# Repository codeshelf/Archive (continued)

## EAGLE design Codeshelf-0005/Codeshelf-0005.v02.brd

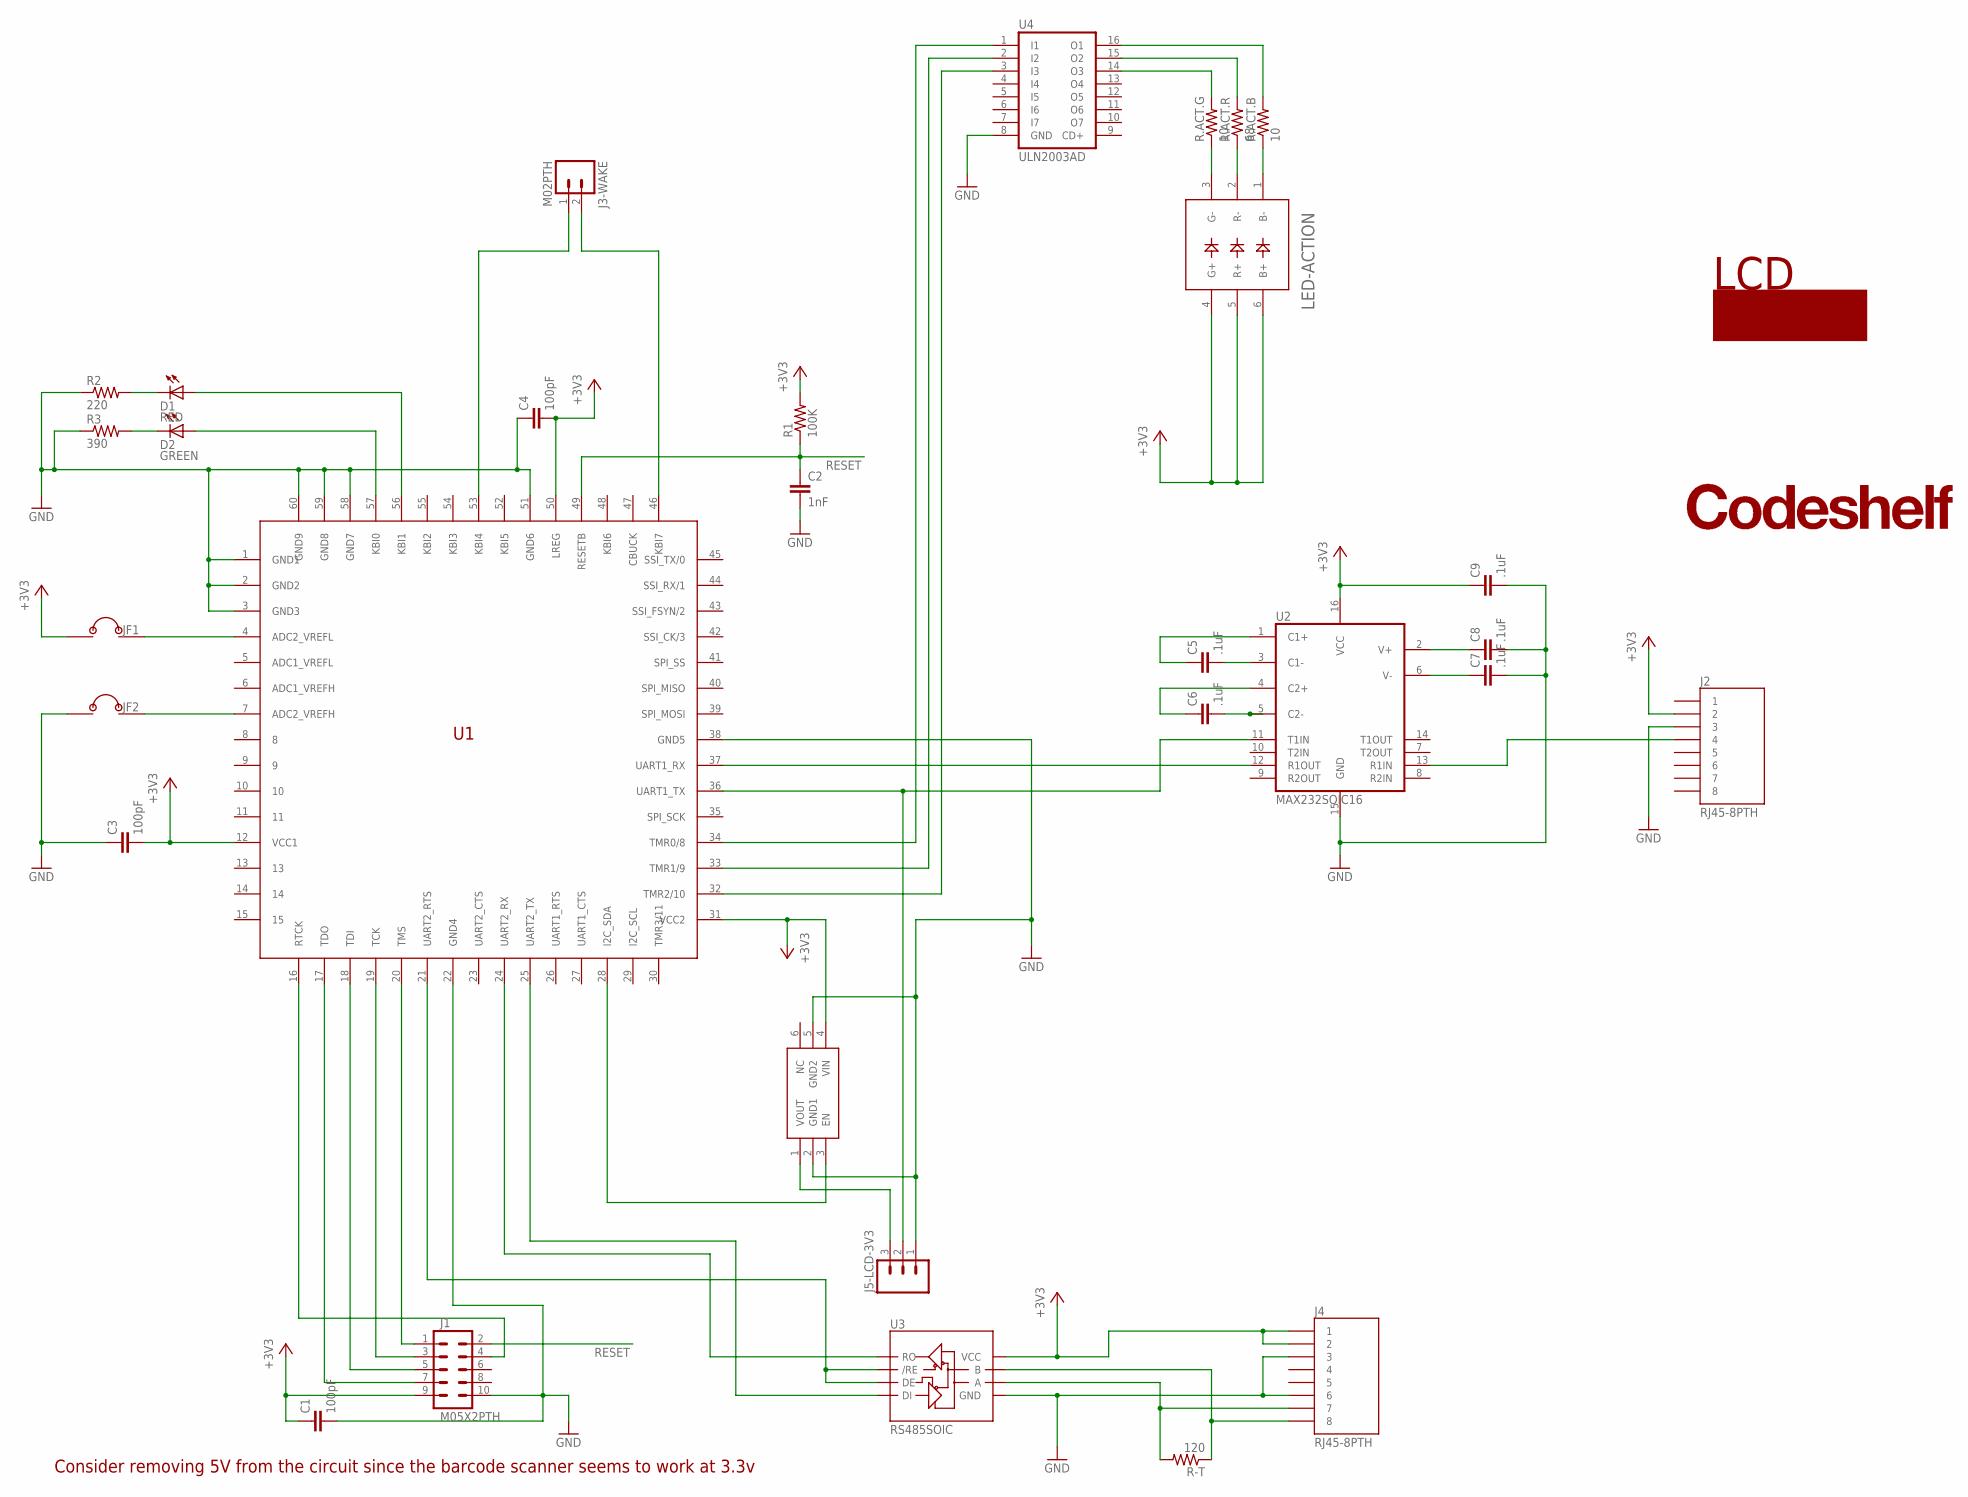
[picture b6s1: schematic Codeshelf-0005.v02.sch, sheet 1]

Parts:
C1, C3, C4: 100pF; C0603
C2: 1nF; C0603
C5, C6, C7, C8, C9: .1uF; C0402
D1: RED; CHIP-LED0805
D2: GREEN; CHIP-LED0805
J1: M05X2PTH; AVR_ICSP
J2, J4: RJ45-8PTH; RJ45-8
J3-WAKE: M02PTH; 1X02
J5-LCD-3V3: M03PTH; 1X03
JF1, JF2: JUMPER-2X-SMT-VIA; JUMPER-VIA-2X
LCD: LCD-SPARKFUN; LCD-20X4-SPARKFUN
LED-ACTION: LED5060A; PLCC-6
LOGO: CODESHELF-LOGO
R1: 100K; RF-R0402
R2: 220; RF-R0402
R3: 390; RF-R0402
R-T: 120; RF-R0402
R.ACT.B, R.ACT.G: 10; RF-R0402
R.ACT.R: 68; RF-R0402
U1: ZSFM201-1A; ZSFM201-1
U2: MAX232SOIC16; SO016
U3: RS485SOIC; SO08
U4: ULN2003AD; SO16
U6: MIC94061C6; SC70-6L

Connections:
+3V3: C1.1, C3.2, C4.2, C9.1, J1.9, J2.2, J4.1, J4.2, JF1.1, LED-ACTION.4 (G+), LED-ACTION.5 (R+), LED-ACTION.6 (B+), R1.2, U1.12 (VCC1), U1.31 (VCC2), U1.50 (LREG), U2.16 (VCC), U3.8 (VCC), U6.4 (VIN); also elsewhere on the board
C1: C5.1, U2.1 (C1+)
C2: C6.1, U2.4 (C2+)
GND: C1.2, C2.2, C3.1, C4.1, C7.2, C8.2, C9.2, J1.10, J2.3, J4.3, J4.6, J5-LCD-3V3.1, JF2.1, R2.1, R3.1, U1.1 (GND1), U1.2 (GND2), U1.3 (GND3), U1.22 (GND4), U1.38 (GND5), U1.51 (GND6), U1.58 (GND7), U1.59 (GND8), U1.60 (GND9), U2.15 (GND), U3.5 (GND), U4.8 (GND), U6.2 (GND1), U6.5 (GND2); also elsewhere on the board
unnamed: D2.A, U1.57 (KBI0)
unnamed: D1.A, U1.56 (KBI1)
unnamed: D2.C, R3.2
unnamed: D1.C, R2.2
unnamed: JF2.2, U1.7 (ADC2_VREFH)
unnamed: JF1.2, U1.4 (ADC2_VREFL)
unnamed: C5.2, U2.3 (C1-)
unnamed: U1.28 (I2C_SDA), U6.3 (EN)
unnamed: J5-LCD-3V3.3, U6.1 (VOUT)
unnamed: C6.2, U2.5 (C2-)
unnamed: C7.1, U2.6 (V-)
unnamed: J3-WAKE.2, U1.46 (KBI7)
unnamed: C8.1, U2.2 (V+)
unnamed: J3-WAKE.1, U1.53 (KBI4)
unnamed: U1.25 (UART2_TX), U3.4 (DI)
unnamed: U1.24 (UART2_RX), U3.1 (RO)
unnamed: U1.21 (UART2_RTS), U3.2 (/RE), U3.3 (DE)
unnamed: J4.8, R-T.1, U3.7 (B)
unnamed: J4.7, R-T.2, U3.6 (A)
unnamed: R.ACT.R.2, U4.15 (O2)
unnamed: R.ACT.G.2, U4.14 (O3)
unnamed: LED-ACTION.1 (B-), R.ACT.B.1
unnamed: LED-ACTION.2 (R-), R.ACT.R.1
unnamed: LED-ACTION.3 (G-), R.ACT.G.1
unnamed: U1.34 (TMR0/8), U4.1 (I1)
unnamed: U1.33 (TMR1/9), U4.2 (I2)
unnamed: R.ACT.B.2, U4.16 (O1)
unnamed: U1.32 (TMR2/10), U4.3 (I3)
R1IN: J2.4, U2.13 (R1IN)
R1OUT: U1.37 (UART1_RX), U2.12 (R1OUT)
RESET: C2.1, J1.2, R1.1, U1.49 (RESETB)
RTCK: J1.4, U1.16 (RTCK)
T1IN: J5-LCD-3V3.2, U1.36 (UART1_TX), U2.11 (T1IN)
TCK: J1.3, U1.19 (TCK)
TDI: J1.5, U1.18 (TDI)
TDO: J1.7, U1.17 (TDO)
TMS: J1.1, U1.20 (TMS)

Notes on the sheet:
Consider removing 5V from the circuit since the barcode scanner seems to work at 3.3v

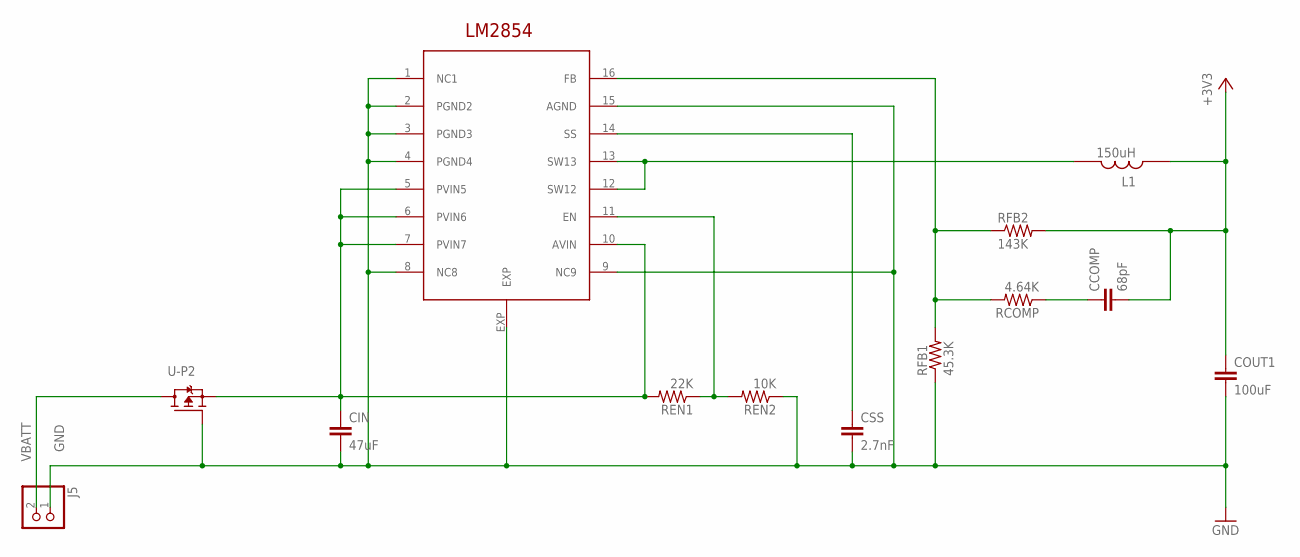
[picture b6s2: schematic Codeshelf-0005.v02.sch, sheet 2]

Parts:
CCOMP: 68pF; C0805
CIN: 47uF; C1210K
COUT1: 100uF; C1210K
CSS: 2.7nF; C0805
J5: PINHD-1X2/90; 1X02/90
L1: 150uH; SLF10165
RCOMP: 4.64K; RF-R0402
REN1: 22K; RF-R0402
REN2: 10K; RF-R0402
RFB1: 45.3K; RF-R0402
RFB2: 143K; RF-R0402
U-P1: LM2854MH; HTSSOP16PWP
U-P2: PCHANNEL-MOSFET-DPAK; DPAK

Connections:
+3V3: CCOMP.2, COUT1.1, L1.2, RFB2.2; also elsewhere on the board
GND: CIN.2, COUT1.2, CSS.2, J5.1, REN2.1, RFB1.1, U-P1.1 (NC1), U-P1.2 (PGND2), U-P1.3 (PGND3), U-P1.4 (PGND4), U-P1.8 (NC8), U-P1.9 (NC9), U-P1.15 (AGND), U-P1.EXP, U-P2.1 (G); also elsewhere on the board
unnamed: CSS.1, U-P1.14 (SS)
unnamed: L1.1, U-P1.12 (SW12), U-P1.13 (SW13)
unnamed: RCOMP.2, RFB1.2, RFB2.1, U-P1.16 (FB)
unnamed: CCOMP.1, RCOMP.1
unnamed: REN1.1, REN2.2, U-P1.11 (EN)
V-PROT: CIN.1, REN1.2, U-P1.5 (PVIN5), U-P1.6 (PVIN6), U-P1.7 (PVIN7), U-P1.10 (AVIN), U-P2.3 (S)
VBATT: J5.2, U-P2.4 (D)

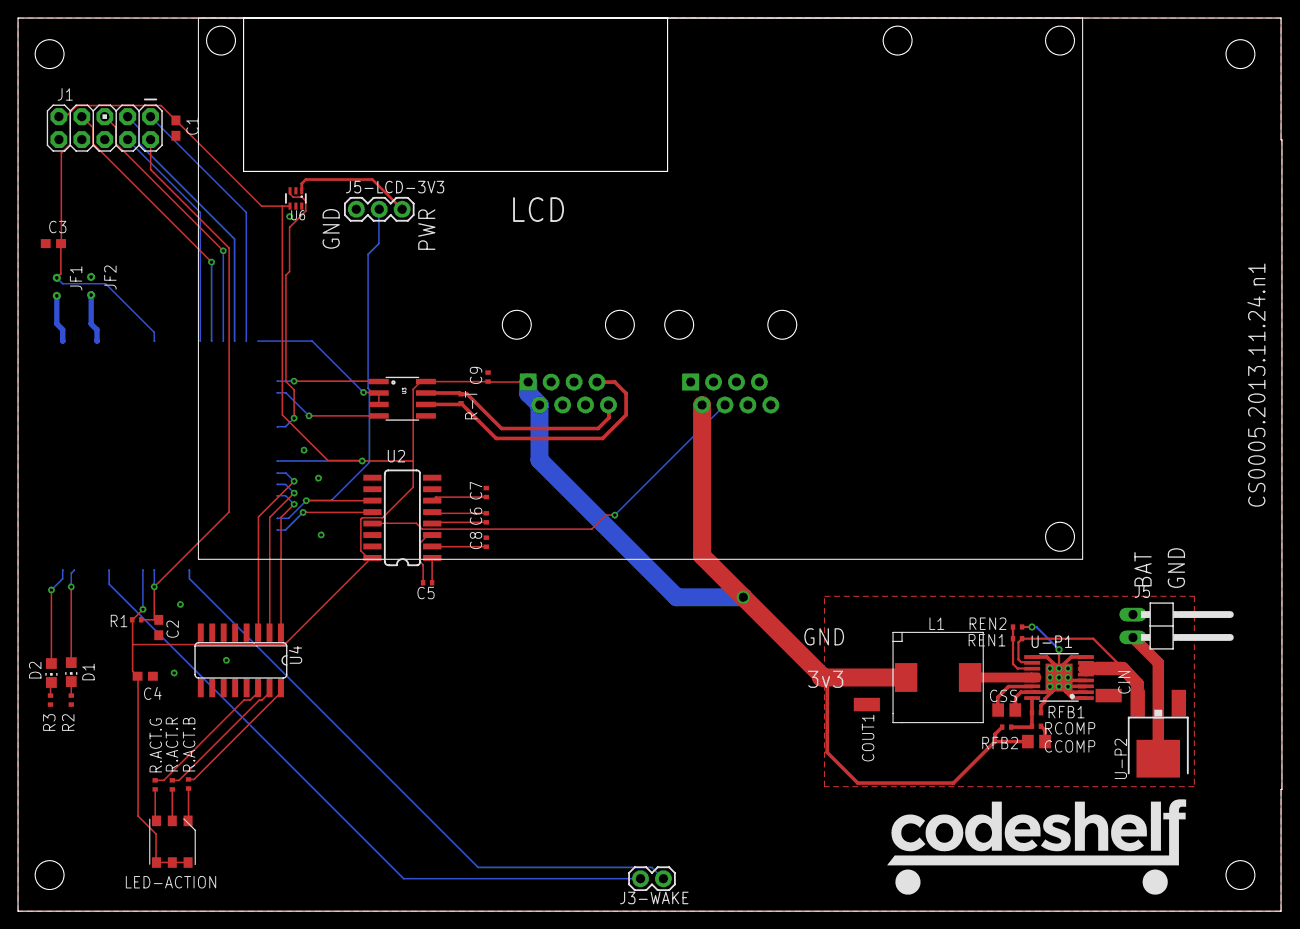
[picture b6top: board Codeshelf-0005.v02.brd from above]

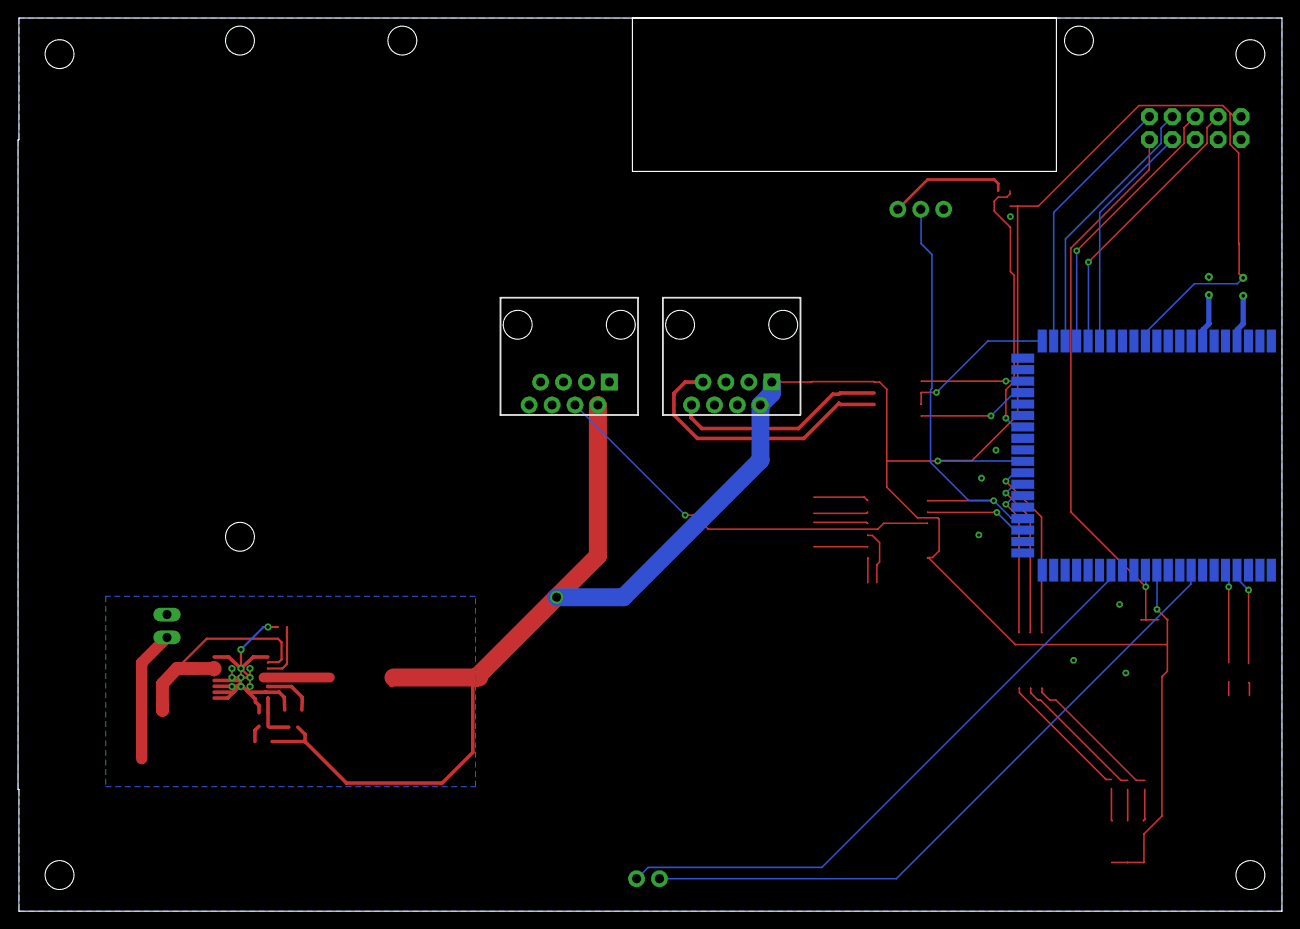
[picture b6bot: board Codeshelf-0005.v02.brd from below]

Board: 2 copper layers, 140.1 x 99.0 mm, 46 parts (3 on the bottom side), 48 nets.

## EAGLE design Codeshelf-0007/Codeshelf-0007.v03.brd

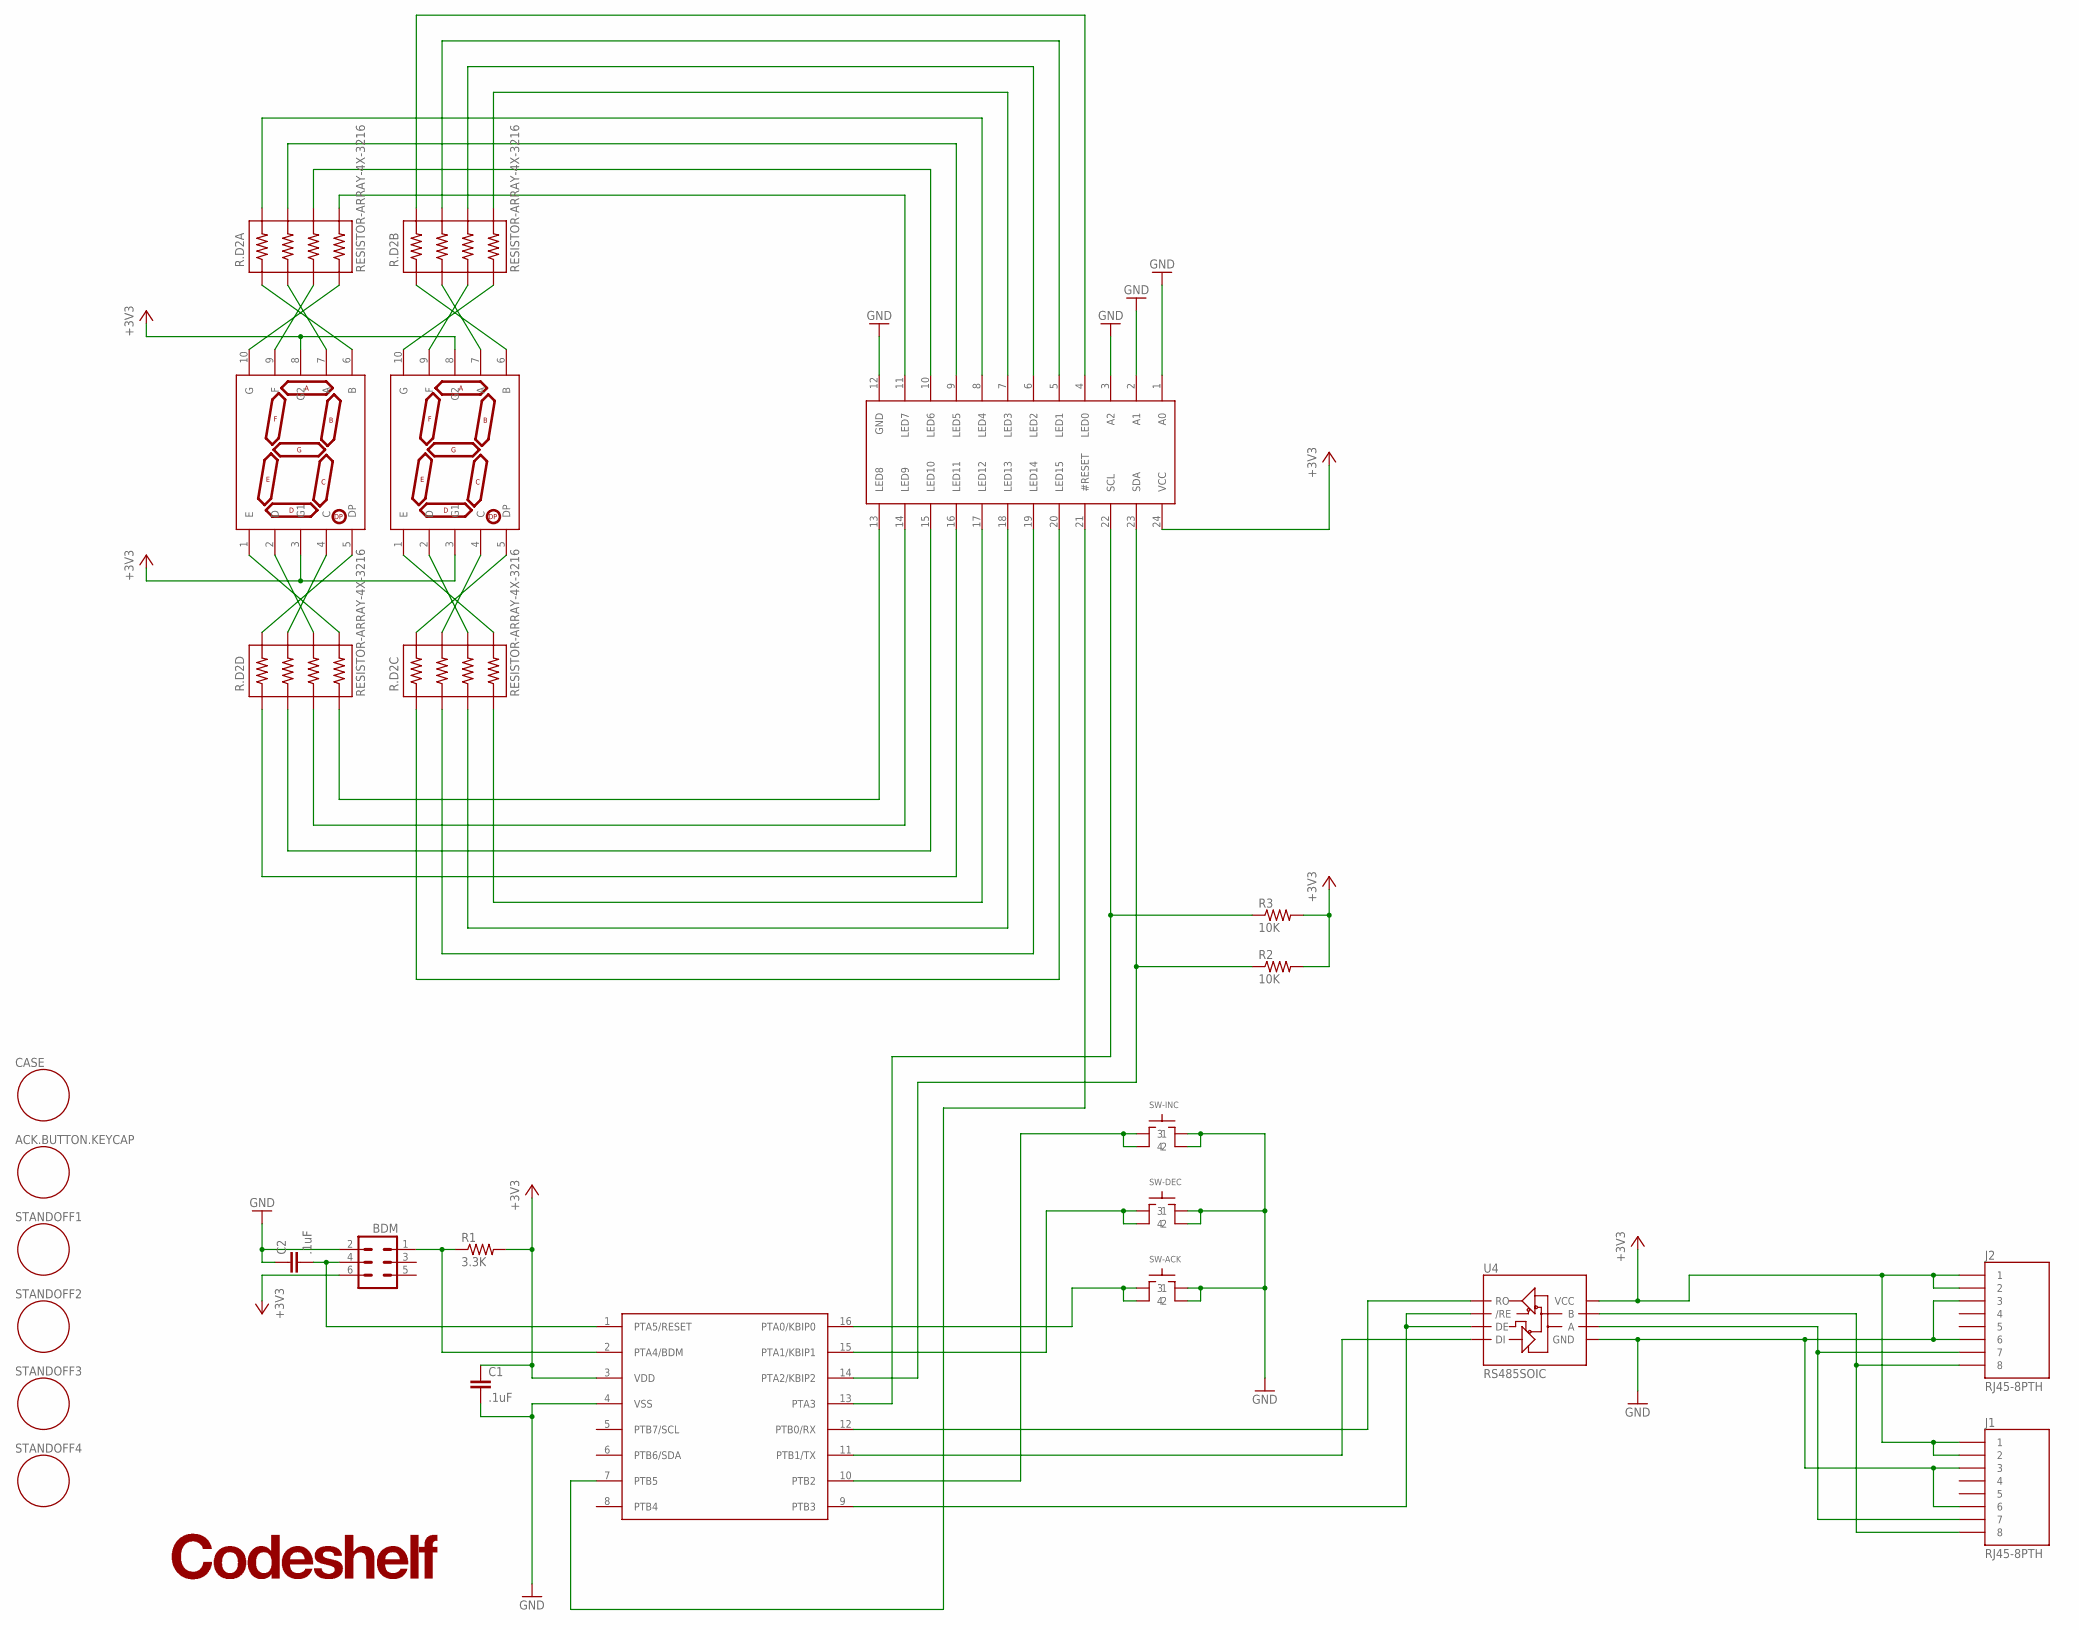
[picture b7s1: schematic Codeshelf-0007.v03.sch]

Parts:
ACK.BUTTON.KEYCAP: EXTERNAL-COMPONENT
BDM: HEADER-3X2
C1, C2: .1uF; C0402
CASE: EXTERNAL-COMPONENT; MFGP PN-1321-C
J1, J2: RJ45-8PTH; RJ45-8
LED1, LED2: 7SEGMENT-1DIGITSMD; 7SEGMENT-1DIG-.40-SMD
LOGO: CODESHELF-LOGO
R1: 3.3K; RF-R0402
R2, R3: 10K; RF-R0402
R.D2A, R.D2B, R.D2C, R.D2D: RESISTOR-ARRAY-4X-3216; 3216-4X
STANDOFF1, STANDOFF2, STANDOFF3, STANDOFF4: EXTERNAL-COMPONENT
SW-ACK: SWITCH-TACTILE-320.03E11
SW-DEC: SWITCH-TACTILE-FSM
SW-INC: SWITCH-TACTILE-FSM
U2: MC9S08QG-DT; TSSOP16
U3: CAT9552; TSSOP24
U4: RS485SOIC; SO08

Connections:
+3V3: BDM.6, C1.1, J1.1, J1.2, J2.1, J2.2, LED1.3 (G1), LED1.8 (G2), LED2.3 (G1), LED2.8 (G2), R1.2, R2.2, R3.2, U2.3 (VDD), U3.24 (VCC), U4.8 (VCC)
GND: BDM.2, C1.2, C2.1, J1.3, J1.6, J2.3, J2.6, SW-ACK.P$3 (3), SW-ACK.P$4 (4), SW-DEC.P$3 (3), SW-DEC.P$4 (4), SW-INC.P$3 (3), SW-INC.P$4 (4), U2.4 (VSS), U3.1 (A0), U3.2 (A1), U3.3 (A2), U3.12 (GND), U4.5 (GND)
unnamed: R.D2A.5 (4B), U3.11 (LED7)
unnamed: R.D2A.6 (3B), U3.10 (LED6)
unnamed: R.D2A.7 (2B), U3.9 (LED5)
unnamed: R.D2A.8 (1B), U3.8 (LED4)
unnamed: R.D2B.5 (4B), U3.7 (LED3)
unnamed: SW-ACK.P$1 (1), SW-ACK.P$2 (2), U2.16 (PTA0/KBIP0)
unnamed: SW-DEC.P$1 (1), SW-DEC.P$2 (2), U2.15 (PTA1/KBIP1)
unnamed: SW-INC.P$1 (1), SW-INC.P$2 (2), U2.10 (PTB2)
unnamed: BDM.1, R1.1, U2.2 (PTA4/BDM)
unnamed: R.D2B.6 (3B), U3.6 (LED2)
unnamed: R.D2B.7 (2B), U3.5 (LED1)
unnamed: R.D2B.8 (1B), U3.4 (LED0)
unnamed: LED2.6 (B), R.D2A.1 (1A)
unnamed: LED2.7 (A), R.D2A.2 (2A)
unnamed: LED2.9 (F), R.D2A.3 (3A)
unnamed: LED2.10 (G), R.D2A.4 (4A)
unnamed: LED2.5 (DP), R.D2D.8 (1B)
unnamed: LED2.4 (C), R.D2D.7 (2B)
unnamed: U2.9 (PTB3), U4.2 (/RE), U4.3 (DE)
unnamed: LED2.2 (D), R.D2D.6 (3B)
unnamed: LED2.1 (E), R.D2D.5 (4B)
unnamed: LED1.6 (B), R.D2B.1 (1A)
unnamed: BDM.4, C2.2, U2.1 (PTA5/RESET)
unnamed: LED1.7 (A), R.D2B.2 (2A)
unnamed: LED1.9 (F), R.D2B.3 (3A)
unnamed: LED1.10 (G), R.D2B.4 (4A)
unnamed: LED1.5 (DP), R.D2C.8 (1B)
unnamed: LED1.4 (C), R.D2C.7 (2B)
unnamed: LED1.2 (D), R.D2C.6 (3B)
unnamed: LED1.1 (E), R.D2C.5 (4B)
unnamed: R.D2D.4 (4A), U3.13 (LED8)
unnamed: R.D2D.3 (3A), U3.14 (LED9)
unnamed: R.D2D.2 (2A), U3.15 (LED10)
unnamed: R.D2D.1 (1A), U3.16 (LED11)
unnamed: R.D2C.4 (4A), U3.17 (LED12)
unnamed: R.D2C.3 (3A), U3.18 (LED13)
unnamed: R.D2C.2 (2A), U3.19 (LED14)
unnamed: R.D2C.1 (1A), U3.20 (LED15)
RESET: U2.7 (PTB5), U3.21 (#RESET)
RS485_N: J1.8, J2.8, U4.7 (B)
RS485_P: J1.7, J2.7, U4.6 (A)
RX: U2.12 (PTB0/RX), U4.1 (RO)
SLA: R2.1, U2.14 (PTA2/KBIP2), U3.23 (SDA)
SLC: R3.1, U2.13 (PTA3), U3.22 (SCL)
TX: U2.11 (PTB1/TX), U4.4 (DI)

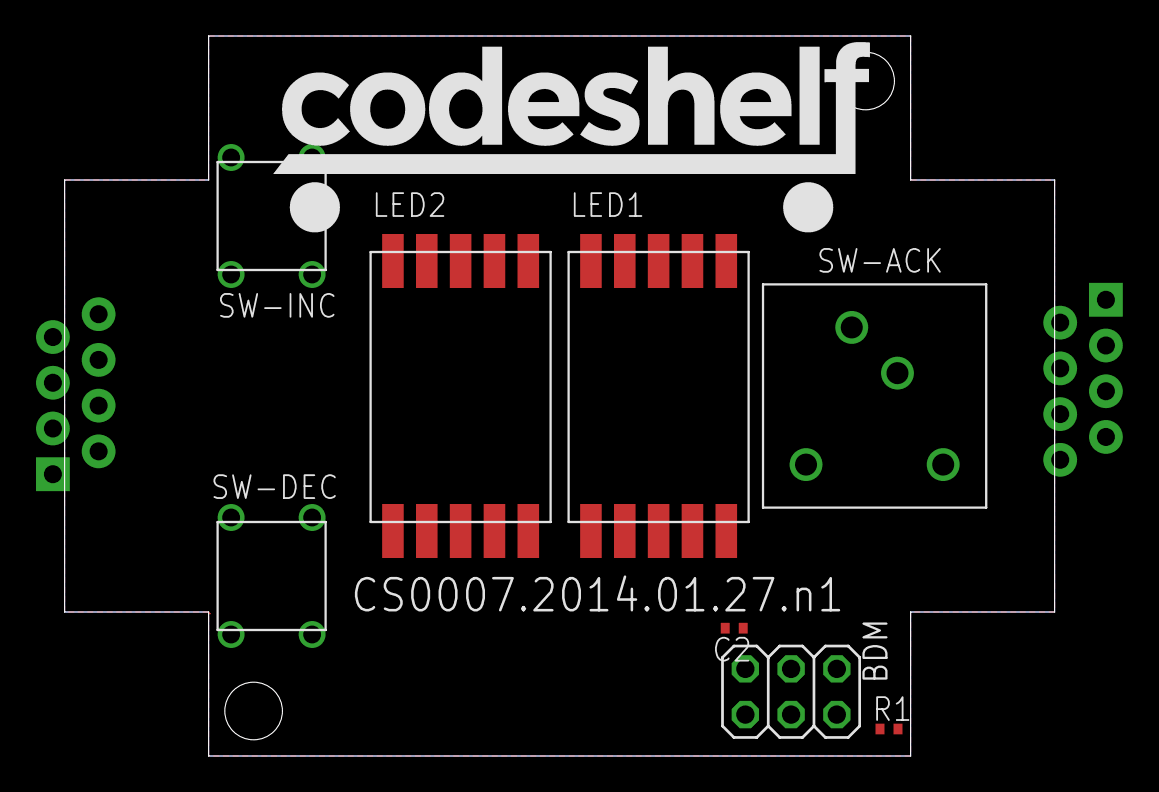
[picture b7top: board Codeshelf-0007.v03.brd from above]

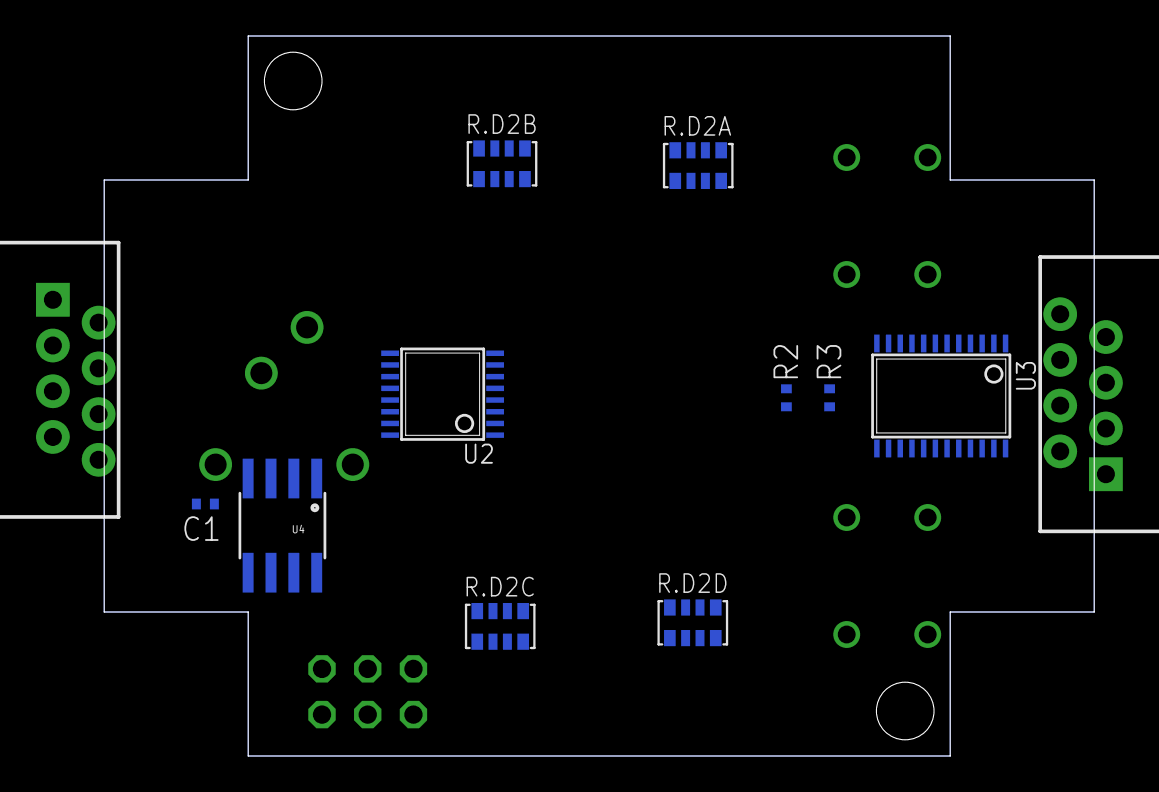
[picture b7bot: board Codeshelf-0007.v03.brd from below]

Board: 2 copper layers, 55.0 x 40.0 mm, 27 parts (12 on the bottom side), 47 nets.

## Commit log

2013-10-22 First commit
    Converted the CAD files to Eagle 6.5 XML project files and committed
    them to the repo.
2013-10-23 cleanup repo
    Cleaned up repo.
    Cleaned up GW-devices.lbr
    Add CS0012 - gateway dongle
    CS0011 board changed to match laser from Laser66.
2013-10-23 Flip the JTAG port
    flip the JTAG port.
    Change the LCD holes from pads to drills.
2013-11-05 Changes related to design review with Ravi and Charlie.
    Mainly we need a new way to connect all of the boards where the cables
    enter the back.
2013-11-23 CHE controller changes for Ravi & Charlie feedback
    RS485 3V/GND on two conductors
    Scanner pins separated from RS485 pins on EN patch cables.
    Sleep switch and power control of scanner the LCD display
2013-11-23 Position controller bus rewiring
    The position controller's RS495 bus rewired to support double 3.3V/GND
    and to be off of the same pins as the scanner. (Matches the change
    with the CHE controller.)
2013-11-24 Move the scanner and rs485 connectors to fit around either battery holder type
2013-11-25 Changes reviewed with Charlie
2013-11-27 BOM review before first articles of 0005, 0007, 0008, 0012
    Reviewed BOM with Charlie
2013-11-29 BOMs as Excel files
2013-11-30 ignore xlsx# files.
2013-11-30 gitignore fixup
2013-11-30 Parts changes for C1, C2 and C7
2014-03-31 New position controller design
2014-03-31 New KW2 Radio design
    First schematic and test layout
2014-04-11 Remove 5V SMPS
2014-04-15 Add CAM files
2014-05-23 SlotFlex Pos. Controller, SMPS
    Copied position controller elements to Slotflex schematic. Corrected
    inductor value typo in SMPS.
2014-05-27 Fixed FB resistor label
    Made FB1/FB2 resistor label consistent with datasheet. but NOT with
    online calculator
2014-06-17 Added Zigbee.lbr (contains KW2)
2014-06-17 Exported libs from schem (KW2)
2014-06-18 Added & modified libraries for LNA parts
2014-06-20 KW2 and Slotflex edits
    Removed RTC crystal from KW2, fixed (connected) switches in schematic of
    0009.v02 and Slotflex v3 with RJ45 with NEW pinout (compatible with new
    scanner pinout which doesn't exist yet in a CHE).
2014-06-21 Started new SlotFlex Layout
2014-06-23 Changed to SMD RJ45
    Working on layout with new RJ45
2014-07-15 Position controller CAD models
    Worked on exporting CAD models from Eagle for Marc. Chose form factor
    for current version of small position controllers (NEMA enclosure lid)
2014-07-23 Targeting final PosController design
    Moved everything to origin to make symmetric, screw hole locations and
    partially complete layout. CAD models for this iteration.
2014-07-30 Finishing routing
    Last few traces still incomplete.
2014-08-05 Gateway Radio release
    This is the commit released to Sonic.
2014-08-05 Added ECO to release version
    This is the actual release for Sonic - added ECO for recordkeeping.
2014-08-05 Recovered CHE file release
    Organized last CHE production files (laptop theft) into Git, added ECO.
    For Sonic release.
2014-08-07 Fixed CHE release typos
    This fixed version was sent to Calla, corrected typos in BOM and fab
    readme. Retagging as release.
2014-08-07 New PosCon CAD model + routing
    Added latest CAD model (sent to Marc) and did a little bit of routing.
2014-08-08 Updated Aisle Controller files
    Made CS008 consistent with past history (old BOMs now match), added ECO
    file, BOM and fab readme for current version.
2014-08-08 Aisle Controller release
    Deleted old files (post-earlier commit), renamed to lose version
    numbering. This is tag / version CS0008.v3.
2014-08-08 Aisle Controller release update
    Missed a zero in ECO file name. This is the new version for tagging
2014-08-18 New PosCon finished routing
    Added RJ45 programming and awaiting new LED test.
2014-08-26 Switched LED
    Exchanged for WS2812 and reroute to match old PosCon pin assigments for
    firmware compatibility.
2014-08-30 Completed new PosCon
    Added BOM (csv and excel) and prepared bottom silkscreen.
2014-09-02 New PosCon tnames change
    Changed tnames layer so Silver knows what the refdes for top layer
    components are. Not on silkscreen.
2014-09-03 Created POSCON.PCB
    New PositionController in new naming scheme (copied and renamed from
    CS0009.v03)
2014-09-03 Fixed BOM
    Fixed PCA9552 P/N, Eswitch price, RGB LED DNP and BOM format.
2014-09-13 PosCon Gerbers, Laser PCB
    Also added some components to GW-Devices
2014-09-15 Finished laser layout
    Had to use one via. Will try and optimize it out later
2014-09-16 Renamed KW2 & moved files around
    Renamed Codeshelf-0013 to KW2CPU.PCB, updated KW2 library with RF6555
    (work in progress for passives)
2014-09-18 LasCon, KW2 Frontend
    Exported LasCon for Jeff, made "wide" version for milling test.
    Schematic for KW2 front end in progress, missing F and ant connector.
    Updated KW2 and GW libs with frontend parts
2014-09-24 Added LED & 3rd laser
    Added LED and 3rd laser, with pingpong ball outline
2014-09-25 Completed laser board
    Finished routing, may need to redo flipped.
2014-09-25 Laser board millable outline
    Changed outline to mill layer. Last version of this orientation, need to
    flip LED head direction
2014-09-25 Flipped LasCon
    Reversed orientation, small traces though
2014-10-01 KW2 antenna, LasCon panel, PosCon fiducials
    Added vertical MMCX connector to KW2 design & library; added panelized
    version of LasCon (old and new design); added Adafruit library and
    fiducials to new PosCon
2014-10-02 Test Commit
    Created two folders and added BOM
    POSCON
    -POSCON Housing BOM
    POSCON.FACE
2014-10-02 LasCon 3D
    Sketchup model of blank PCB (and stl and dae)
2014-10-02 Consolidated libraries
    Moved all top-level Eagle libraries into one folder, moved top-level
    .ULP, .CAM and .dru files into CAM_ULP
2014-10-02 POSCON 1st Commit
    Created Following:
    POSCON.BACK
    -Poscon Backplate .dxf and .pdf Drawings
    POSCON FACE
    -POSCON Faceplate RB22 .dxf and .pdf Drawings
    Updated POSCON BOM file
2014-10-10 PosCon parts, KW2 frontend, LasCon
    Added part numbers for orange display, black buttons to PosCon. Worked
    on frontend layout for KW2 and produced a new version of LasCon
2014-10-10 LasCon BOM
    Updated LasCon parts
2014-10-10 Moved LASCON.PCB
    Moved LASCON.PCB to its own repo
2014-10-11 Added DF12 connector, moved PosCon
    Still need device for DF12_F, moved PosCon.PCB to own repo
2014-10-12 Brain component placement
    Almost finished KW2CPU component placement. Needs JTAG and memory
2014-10-12 Moved KW2CPU
    Moved KW2CPU.PCB to its own repo and deleted this one
2014-10-14 Moved POSCON MECH
    Moved POSCON FACE, BACK files to own repo, deleted from here
2014-10-22 DF12
    Various DF12 / JTAG connectors added & modified.
2014-11-05 Added schematic fixes for RFMD
2014-11-14 Latest
    Not sure what changed. Measured / looked up some name things but didn't
    modify anything I know of
2015-01-06 Updated CAM file, added & fixed parts
    Added dimension layer to each file in 2-layer CAM file; fixed KW2 pin
    typo added some components
2015-01-06 Added SH variant
2015-01-28 Updated / added various components
    Update
2015-05-18 Moved libraries to new repo
